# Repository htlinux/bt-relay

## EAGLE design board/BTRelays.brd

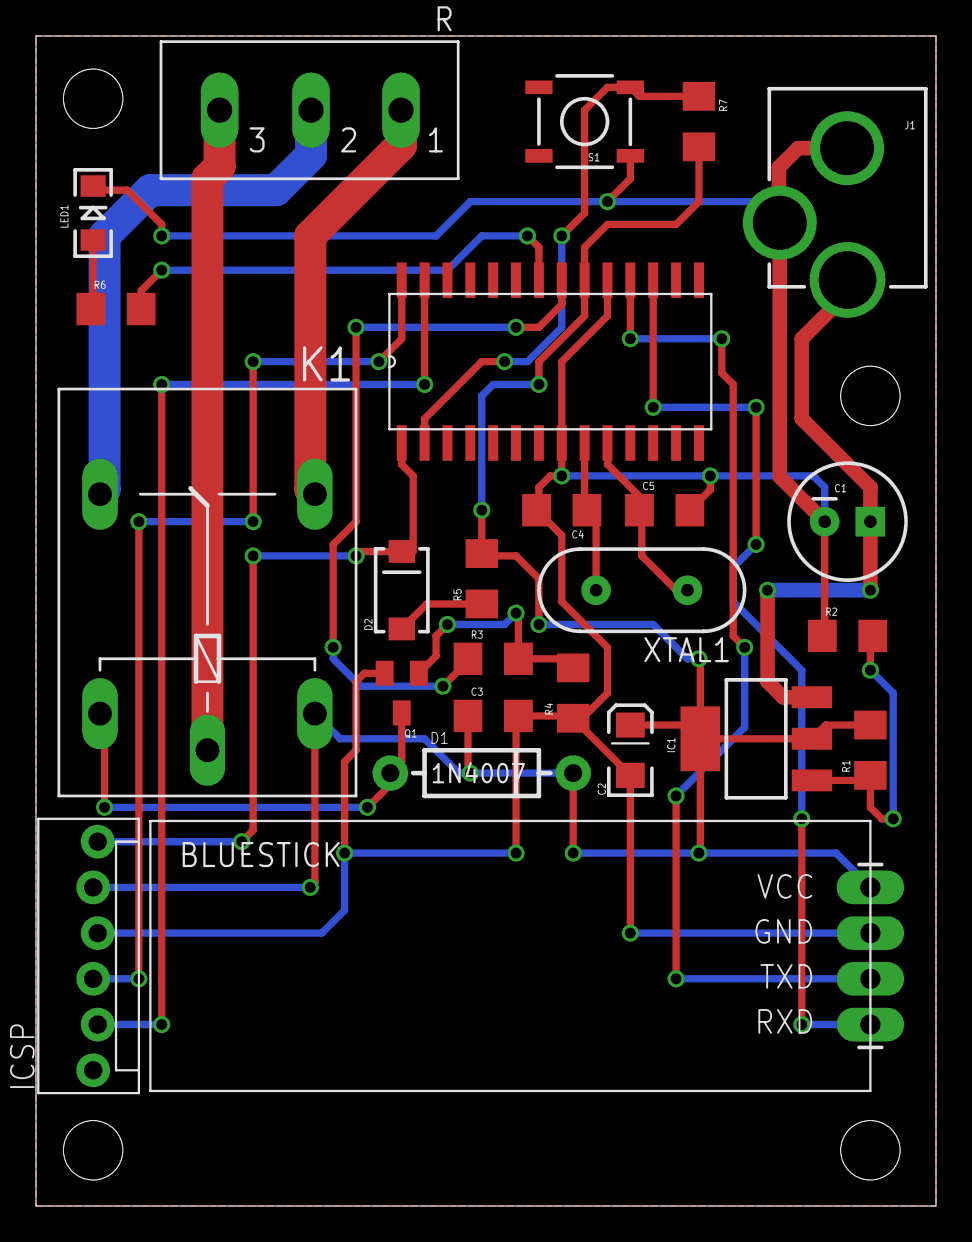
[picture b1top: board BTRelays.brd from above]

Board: 2 copper layers, 50.0 x 65.0 mm, 29 parts (0 on the bottom side), 21 nets.

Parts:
BLUESTICK: BLUESTICK; BLUESTICK-PTH
C1: 100uF; CPOL-RADIAL-100UF-25V
C2: 10uF; EIA3216
C3: 100nF; 1206
C4, C5: 22pF; 1206
D1: 1N4007; DIODE-1N4001
D2: SMA-DIODE
IC1: LD1117; SOT223
IC2: PIC18F252-X/SO; SOIC28-W_MC
ICSP: MOLEX-1X6_LOCK
J1: POWER_JACKPTH_LOCK; POWER_JACK_PTH_LOCK
JP1, JP2, JP3, JP4: STAND-OFF
K1: G5L; G5LE
LED1: LED-1206
Q1: MMBT2222A; SOT23
R: MSTBV3
R1: 200; 1206
R2: 600; 1206
R3: 4.7K; 1206
R4, R7: 47K; 1206
R5: 10K; 1206
R6: 220; 1206
S1: TACTILE_SWITCH_SMD
XTAL1: 20Mhz; HC49US

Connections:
5V: BLUESTICK.VCC, C2.A, C3.1, D1.C, IC1.2, IC1.4, IC2.20, ICSP.5, K1.1, R1.2, R5.2, R7.2
BTN1: IC2.2, R7.1, S1.3
BT_RXD: BLUESTICK.RXD, IC2.17
BT_TXD: BLUESTICK.TXD, IC2.18
GND: BLUESTICK.GND, C1.2, C2.C, C3.2, C4.2, C5.2, IC2.8, IC2.19, ICSP.4, J1.GND, J1.GNDBREAK, LED1.C, Q1.2, R2.1, R4.1, S1.1
unnamed: C1.1, IC1.3, J1.PWR
unnamed: IC1.1, R1.1, R2.2
unnamed: Q1.1, R3.2, R4.2
unnamed: D1.A, K1.2, Q1.3
unnamed: K1.P, R.3
unnamed: K1.O, R.2
unnamed: K1.S, R.1
unnamed: D2.C, IC2.1, ICSP.6
unnamed: D2.A, R5.1
unnamed: LED1.A, R6.1
unnamed: IC2.22, R6.2
OSC1: C4.1, IC2.9, XTAL1.2
OSC2: C5.1, IC2.10, XTAL1.1
PGC: IC2.27, ICSP.2
PGD: IC2.28, ICSP.3
RELAY1: IC2.21, R3.1

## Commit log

2013-05-15 Initial directory structure.
2013-05-15 Board files in Eagle PCB
2015-03-24 Migrating wiki contents from Google Code
